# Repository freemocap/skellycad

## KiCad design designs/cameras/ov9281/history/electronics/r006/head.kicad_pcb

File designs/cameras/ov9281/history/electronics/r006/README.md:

# R06 power and ground routing

R06 adds saved copper to the R05 controller, sensor head and flex. It is a
checked routing draft, **not a fabrication release or a demonstrated camera**.
Open `controller.kicad_pcb` to inspect the power work, `head.kicad_pcb` for the
sensor, or `assembly-interconnect-study.kicad_pcb` for the flat assembly.
The combined assembly file is for inspection only; manufacture would use
three separate board definitions after the remaining engineering is complete.

## What changed

- Added 199 through vias and verified 219 component-pad-to-via paths.
- Added ground planes on the second copper layer of both rigid boards.
  All 75 controller ground pads join one electrical group. On the head,
  32 of 40 ground pads connect; eight sensor ground pads remain unconnected.
- Added 44 power branches: 37 on the third copper layer and seven on the back.
  Backside bridges join the controller's split 3.3 V fill. Of its 44 supply
  pads, 39 now connect together; five remain isolated.
- Added a continuous front-side ground plane and 18 vias to the flex.
  All 24 end-to-end conductors and all 18 ground contacts pass connectivity
  checks. Connector fingers remain exposed on the back.
- Defined provisional layer thicknesses in the native boards: 0.60 mm rigid
  and 0.10 mm flex for copper plus dielectric. These are design assumptions,
  not supplier-approved stackups. Mask, coverlay and adhesive remain additional.

The four-layer strategy follows Espressif's guidance: ground on layer 2 and
power on layer 3. The candidate inner core-supply and USB-input routes use
0.508 mm and 0.635 mm widths respectively. Other power routes use 0.254 mm.
The local surface escapes are still 0.15 mm; this does not establish compliance
with the recommended power widths, current capacity or decoupling-loop layout
[@esp32P4PcbLayout]. Circuit topology and supply sequencing still need review.

## Checks on the saved files

| KiCad unconnected items | R05 | R06 |
| --- | ---: | ---: |
| Controller | 195 | 54 |
| Sensor head | 93 | 47 |
| Flex | 8 | 0 |

These counts measure missing physical connections, not percentage completion.
There are no short-circuit or clearance violations under the inherited draft
rules. R06 still reports six open camera tracks and nine vias connected on only
one layer. These are unfinished routes, so this is **not a clean fabrication DRC**.
Schematic ERC reports zero violations under the inherited project settings;
ignored categories are visible in `checks/erc.rpt`.

`validation.json` records native-file hashes, 456 schematic-to-pad net checks,
24 assembled pin-alignment checks, retained R05 geometry and copper, and native
KiCad connectivity groups for every net. A one-pad net is trivially connected
on that board; it does not prove an external connection or a working function.
Filled region counts are geometry counts; physical copper connectivity is
checked separately, including the bridges between 3.3 V regions.

`power-routing.json` records each added escape and power route. It lists 33
pads without an escape and ten attempted power branches left unrouted. These
are diagnostic subsets of the DRC findings, not additional totals to add to
the table. Surface paths use straight or single-bend candidates; power paths
use collision-checked grid searches. Failure means the search did not find a
path, not that the circuit is impossible to route.

## What still separates this from a working camera

Complete the dense sensor/processor escapes, power circuits and camera/control
signal routes. Review placement and the fabrication process before changing
clearances or introducing finer vias. The 0.45 mm via lands and 0.20 mm drills
are provisional; this revision avoids via-in-pad. The small existing package
lands still require process review [@jlcThinPcbCapabilities].

The flex's solid plane changes its stiffness and transmission-line geometry.
No controlled impedance, supply-drop, thermal, flex-life or optical performance
is established. The wider R05 interface, 76 mm flat length, connector stiffener,
solder joint and strain relief also remain unfinished. Optics, IR illumination
and end-to-end capture firmware are separate unfinished parts of this camera.

Review scope, 2026-10-27: Espressif power and layer guidance, local native KiCad
DRC/ERC, filled-zone connectivity and retained R05 interface geometry. No
hardware, signal-integrity, optical or thermal measurements were performed.

## Reproduce and inspect

From the repository root, use KiCad 10's bundled Python to run
`designs/eye-camera-ov9281/build_r06.py --output generated/ov9281-r06-rebuild`.
Choose a new output directory; the builder refuses to replace one. Then run
`designs/eye-camera-ov9281/validate_r06.py --directory generated/ov9281-r06-rebuild`
with the same interpreter. The validator must finish successfully; inspect its
remaining unconnected items rather than treating success as release approval.

For a new FreeCAD review, run
`python designs/eye-camera-ov9281/export_r06_review.py --output generated/ov9281-r06-review-2`
from the repository root using ordinary Python. Choose another new output path
if that directory already exists. The script verifies the saved R06 hashes, exports
actual PCB solids and prepares `open-review.FCMacro`. Follow
`docs/development.md` to send that macro to the verified existing FreeCAD process.
It preserves open documents and saves a separate R06 FCStd. The review contains
substrates and copper, including internal layers; component bodies and optics
are absent. Its flex height is for viewing, not a validated mating height.

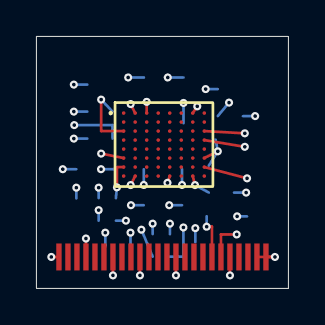
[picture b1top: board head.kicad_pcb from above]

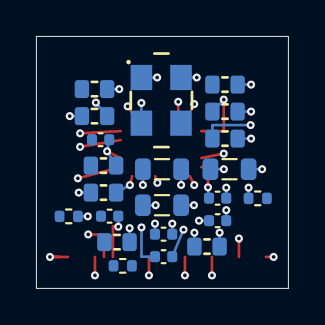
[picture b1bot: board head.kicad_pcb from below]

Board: 4 copper layers, 14.0 x 14.0 mm, 24 parts (22 on the bottom side), 24 nets.

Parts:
C7, C8, C10, C12, C13, C18, C19, C21, C33: C_1u_0603; C_0603_1608Metric
C9, C14, C15, C16, C17, C20: C_100n_6V3_0402; C_0402_1005Metric
J201: SOLDER FLEX / 24 contacts; Flex_Solder_24_P0.5_R05
L1, L2, L3: MLP2012S3R3MT; L_0805_2012Metric
R7, R8, R9: R_0R_0402; R_0402_1005Metric
U1: ImageSensor_OV9281; OV9281
Y1: 7C-24.000MBB-T; Oscillator_SMD_TXC_7C_5x3.2x1.2mm

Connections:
+1V2: J201.17, L1.1
+1V8: C33.1, J201.11, L2.1, Y1.1, Y1.4
+2V8: J201.19, L3.1
/CAM_L_CLK_N: J201.5, U1.H4
/CAM_L_CLK_P: J201.6, U1.G4
/CAM_L_D0_N: J201.2, U1.H3
/CAM_L_D0_P: J201.3, U1.G3
/CAM_L_D1_N: J201.8, U1.F5
/CAM_L_D1_P: J201.9, U1.G5
/CAM_NRST_1V8: J201.15, U1.A5
/M1_AVDD: C18.1, C19.1, C20.1, L3.2, R9.2, U1.B8, U1.C1, U1.G7, U1.G8
/M1_CAM_SCL_1V8: J201.12, U1.E4
/M1_CAM_SDA_1V8: J201.13, U1.A4
/M1_DOVDD: C13.1, C15.1, C16.1, L2.2, R7.1, U1.B7, U1.D3, U1.H2, U1.H6
/M1_DVDD: C9.1, C12.1, C14.1, L1.2, U1.A2, U1.B1, U1.B3, U1.C5, U1.D8, U1.F2, U1.F3, U1.G1, U1.G6, U1.H5
/M1_MCLK: U1.E2, Y1.3
/M1_PVDD: C17.1, R9.1, U1.D5
/M1_SID: R7.2, R8.1, U1.E1
/M1_VH: C21.1, U1.E8
/M1_VN1: C7.1, U1.D7
/M1_VN2: C8.1, U1.E7
/M1_VN3: C10.1, U1.F7
/M1_VSYNC_1V8_M: J201.16, U1.B5
GND: C7.2, C8.2, C9.2, C10.2, C12.2, C13.2, C14.2, C15.2, C16.2, C17.2, C18.2, C19.2, C20.2, C21.2, C33.2, J201.1, J201.4, J201.7, J201.10, J201.14, J201.18, J201.20, J201.23, J201.24, R8.2, U1.A3, U1.A7, U1.B2, U1.C8, U1.D2, U1.E3, U1.E5, U1.E6, U1.F1, U1.F4, U1.F6, U1.F8, U1.G2, U1.H7, Y1.2

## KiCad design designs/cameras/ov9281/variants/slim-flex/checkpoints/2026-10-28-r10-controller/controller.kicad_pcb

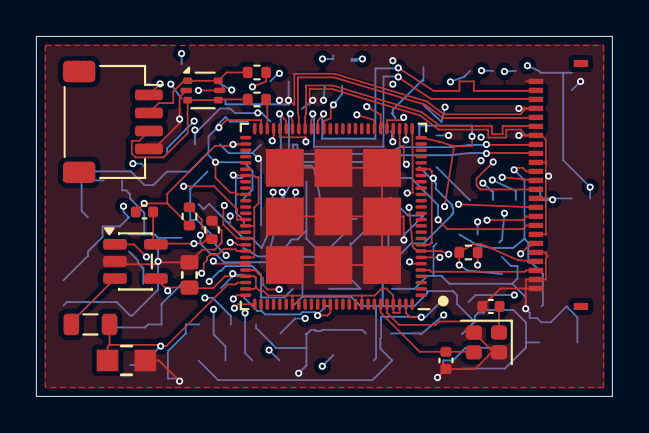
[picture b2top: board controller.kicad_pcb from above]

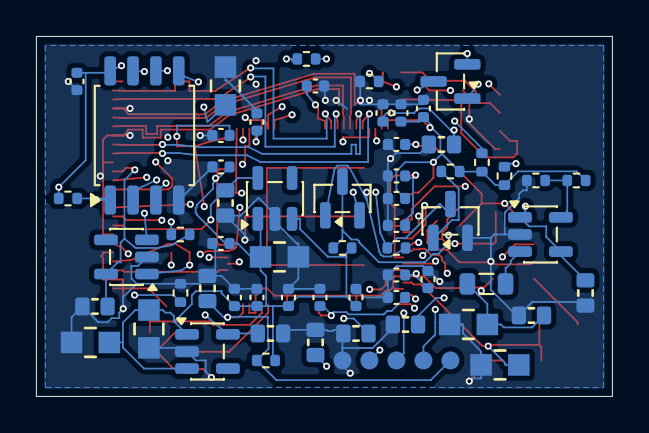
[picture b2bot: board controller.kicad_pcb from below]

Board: 6 copper layers, 32.0 x 20.0 mm, 77 parts (60 on the bottom side), 48 nets.

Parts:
C1, C2, C3: C_4u7_0805; C_0805_2012Metric
C4, C5, C6: C_1u_0603; C_0603_1608Metric
C101, C102: CL_TBD; C_0402_1005Metric
C103, C132, C135: 100n; C_0402_1005Metric
C104, C125, C126, C127, C133: 1u; C_0603_1608Metric
C105, C108, C136: 4.7u; C_0603_1608Metric
C106, C109: 22u; C_0805_2012Metric
C107: 22p; C_0402_1005Metric
C110: 100n / U101.9; C_0402_1005Metric
C111: 100n / U101.21; C_0402_1005Metric
C112: 100n / U101.26; C_0402_1005Metric
C113: 100n / U101.54; C_0402_1005Metric
C114: 100n / U101.62; C_0402_1005Metric
C115: 100n / U101.75; C_0402_1005Metric
C116: 100n / U101.76; C_0402_1005Metric
C117: 100n / U101.77; C_0402_1005Metric
C118: 100n / U101.85; C_0402_1005Metric
C119: 100n / U101.91; C_0402_1005Metric
C120: 100n / U101.96; C_0402_1005Metric
C121: 100n / U101.101; C_0402_1005Metric
C122: 100n / U101.102; C_0402_1005Metric
C123, C124: 10u; C_0805_2012Metric
C128: 100n / U101.30; C_0402_1005Metric
C129: 100n / U101.59; C_0402_1005Metric
C130: 100n / U101.67; C_0402_1005Metric
C131, C134: 10n; C_0402_1005Metric
J101: USB / JST 4-contact candidate; JST_SH_SM04B-SRSS-TB_1x04-1MP_P1.00mm_Horizontal
J102: FH34SRJ-24S-0.5SH(99); Hirose_FH34SRJ_24S_0.5SH_R05
J103: PROGRAM / RESET pads; ProgrammingPads_5x1mm_P1.5mm
L101, L102: 2.2u / Isat TBD; L_0805_2012Metric
Q101, Q102: BSS138; SOT-23
Q103: BSS138 / reset asserted HIGH; SOT-23
R101, R102, R103, R104, R117, R118: 10k; R_0402_1005Metric
R105, R106: 499k; R_0402_1005Metric
R107: 453k; R_0402_1005Metric
R108, R116: 100k; R_0402_1005Metric
R109, R110: 0; R_0402_1005Metric
R111: 4.02k 1%; R_0402_1005Metric
R112, R113, R114, R115: 4.7k; R_0402_1005Metric
U5: TLV73318PDBVT; SOT-23-5
U6: TLV73312PDBVT; SOT-23-5
U7: TLV73328PDBVT; SOT-23-5
U101: ESP32-P4NRW16X / v3.x; ESP32-P4
U102: W25Q32JVSS (4 MB candidate); SOIC-8_5.3x5.3mm_P1.27mm
U103: TLV62569DBV / core; SOT-23-5
U104: TLV62569DBV / system; SOT-23-5
U105: USBLC6-2P6; SOT-666
Y101: 40 MHz / CL TBD; Crystal_SMD_2016-4Pin_2.0x1.6mm

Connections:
+1V2: C6.1, J102.17, U6.5
+1V8: C5.1, J102.11, Q101.1, Q102.1, R112.1, R114.1, R117.1, U5.5
+2V8: C4.1, J102.19, U7.5
+3V3: C1.1, C2.1, C3.1, C105.1, C109.1, C110.1, C111.1, C114.1, C115.1, C117.1, C118.1, C120.1, C121.1, C122.1, C123.1, C134.1, C135.1, C136.1, J102.21, L102.2, R102.1, R103.1, R104.1, R107.1, R113.1, R115.1, R116.1, U5.1, U5.3, U6.1, U6.3, U7.1, U7.3, U101.9, U101.21, U101.51, U101.62, U101.75, U101.77, U101.85, U101.96, U101.101, U101.102, U103.4
/CAM_L_CLK_N: J102.5, U101.45
/CAM_L_CLK_P: J102.6, U101.44
/CAM_L_D0_N: J102.2, U101.42
/CAM_L_D0_P: J102.3, U101.43
/CAM_L_D1_N: J102.8, U101.46
/CAM_L_D1_P: J102.9, U101.47
/CAM_NRST_1V8: J102.15, Q103.3, R117.2
/CAM_RESET_ASSERT: Q103.1, R116.2, U101.6
/CAM_SCL_3V3: Q101.3, R113.2, U101.7
/CAM_SDA_3V3: Q102.3, R115.2, U101.8
/FLASH_CLK: U101.32, U102.6
/FLASH_CS: R101.2, U101.27, U102.1
/FLASH_D: U101.33, U102.5
/FLASH_HOLD: U101.31, U102.7
/FLASH_Q: U101.28, U102.2
/FLASH_WP: U101.29, U102.3
/LED_PWM: J102.22, U101.5
/M1_CAM_SCL_1V8: J102.12, Q101.2, R112.2
/M1_CAM_SDA_1V8: J102.13, Q102.2, R114.2
/M1_VSYNC_1V8_M: J102.16, R118.1
/P4_BOOT: J103.4, R103.2, U101.66
/P4_CSI_REXT: R111.1, U101.48
/P4_DOWNLOAD_ENABLE: R104.2, U101.68
/P4_EN: C104.1, J103.5, R102.2, U101.103
/P4_EN_DCDC: U101.79, U103.1
/P4_FB: C107.2, R105.2, R106.1, U101.78, U103.5
/P4_FLASH_VDD: C103.1, C125.1, C128.1, R101.1, U101.30, U101.71, U102.8
/P4_LDO4_UNUSED: C127.1, U101.74
/P4_MIPI_2V5: C131.1, C132.1, C133.1, U101.41, U101.73
/P4_PSRAM_VDD: C126.1, C129.1, C130.1, U101.59, U101.67, U101.72
/P4_SW: L101.1, U103.3
/P4_UART_RX: J103.3, U101.70
/P4_UART_TX: J103.2, U101.69
/P4_VDD_HP: C106.1, C107.1, C112.1, C113.1, C116.1, C119.1, C124.1, L101.2, R105.1, U101.26, U101.54, U101.76, U101.91
/P4_XTAL_N: C102.1, U101.99, Y101.3
/P4_XTAL_P: C101.1, U101.100, Y101.1
/SYS_FB: R107.2, R108.1, U104.5
/SYS_SW: L102.1, U104.3
/USB_DM: J101.2, R109.1, U105.1, U105.6
/USB_DM_CHIP: R109.2, U101.49
/USB_DP: J101.3, R110.1, U105.3, U105.4
/USB_DP_CHIP: R110.2, U101.50
/USB_VBUS: C108.1, J101.1, U104.1, U104.4, U105.5
GND: C1.2, C2.2, C3.2, C4.2, C5.2, C6.2, C101.2, C102.2, C103.2, C104.2, C105.2, C106.2, C108.2, C109.2, C110.2, C111.2, C112.2, C113.2, C114.2, C115.2, C116.2, C117.2, C118.2, C119.2, C120.2, C121.2, C122.2, C123.2, C124.2, C125.2, C126.2, C127.2, C128.2, C129.2, C130.2, C131.2, C132.2, C133.2, C134.2, C135.2, C136.2, J101.4, J102.1, J102.4, J102.7, J102.10, J102.14, J102.18, J102.20, J102.23, J102.24, J103.1, Q103.2, R106.2, R108.2, R111.2, R118.2, U5.2, U6.2, U7.2, U101.105, U102.4, U103.2, U104.2, U105.2, Y101.2, Y101.4

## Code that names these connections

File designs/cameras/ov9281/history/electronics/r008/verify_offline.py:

"""Recheck the selected artifact bundle; distinguish checks from release gates.

Does not alter native CAD files, flash devices, or report simulated pixels as
camera capture. Run after building both firmware variants with build.py.
"""
from pathlib import Path
import hashlib, json, re, subprocess, sys, xml.etree.ElementTree as ET
from system_analysis import analysis

HERE=Path(__file__).resolve().parent
ROOT=HERE.parents[1]
def sha(p):return hashlib.sha256(p.read_bytes()).hexdigest()

def verify():
    selection=json.loads((HERE/'controller-selection.json').read_text())
    board=HERE/Path(selection['validation']).parent
    validation=json.loads((board/'validation.json').read_text())
    for name,digest in validation['sha256'].items():assert sha(board/name)==digest,name
    parent=json.loads((board/'routing-r08.json').read_text())['parent_sha256']
    for name,digest in parent.items():assert sha(HERE/'electronics/r07'/name)==digest,name
    tree=ET.parse(board/'source-netlist.xml')
    nets={(q.get('ref'),q.get('pin')):n.get('name') for n in tree.findall('.//nets/net') for q in n}
    source=(HERE/'firmware/main/camera_main.c').read_text()
    bindings={'LED_GPIO':'/LED_PWM','RESET_ASSERT_GPIO':'/CAM_RESET_ASSERT',
              'SCL_GPIO':'/CAM_SCL_3V3','SDA_GPIO':'/CAM_SDA_3V3'}
    checked={}
    for constant,net in bindings.items():
        pin=re.search(r'\b'+constant+r'\s*=\s*(\d+)',source).group(1)
        assert nets[('U101',pin)]==net
        checked[constant]={'gpio':int(pin),'schematic_net':net}
    assert nets[('Q103','1')]==nets[('U101','6')]
    assert nets[('Q103','2')]=='GND'
    assert nets[('Q103','3')]==nets[('U1','A5')]
    assert nets[('R8','1')]==nets[('U1','E1')]
    assert nets[('R8','2')]=='GND'
    comps={x.get('ref'):x for x in tree.findall('.//components/comp')}
    assert comps['R7'].find("property[@name='dnp']") is not None
    assert comps['R8'].find("property[@name='dnp']") is None
    assert 'CONFIG_CAMERA_OV9281_SID_LOW=y' in (HERE/'firmware/sdkconfig.defaults').read_text()
    builds={}
    for mode in ['sensor','synthetic']:
        folder=ROOT/'generated'/('camera-firmware-'+mode)
        record=json.loads((folder/'build-report.json').read_text())
        assert record['compiled'] and not record['executed_on_hardware']
        for name,digest in record['source_sha256'].items():assert sha(HERE/'firmware'/name)==digest,name
        for name,digest in record['binary_sha256'].items():assert sha(folder/'build'/name)==digest,name
        config=(folder/'sdkconfig').read_text()
        assert 'CONFIG_ESP32P4_REV_MIN_FULL=300' in config
        assert 'CONFIG_TINYUSB_RHPORT_HS=y' in config
        assert ('CONFIG_SKELLY_SYNTHETIC=y' in config)==(mode=='synthetic')
        builds[mode]=record
    tests=subprocess.run([sys.executable,'-B','-m','unittest','discover','-s',str(HERE/'firmware/host'),'-p','test_*.py','-v'],capture_output=True,text=True)
    assert tests.returncode==0,tests.stdout+tests.stderr
    # The linked binary has no camera codec/IPA or radio blob library. This is
    # a narrow map check, not a legal audit of every toolchain runtime object.
    linkmap=(ROOT/'generated/camera-firmware-sensor/build/skelly_eye_camera.map').read_text()
    excluded=['libesp_ipa.a','libesp_h264.a','libnet80211.a','libpp.a','libcoexist.a','libesp_wifi.a']
    assert all(name not in linkmap for name in excluded)
    inventory=json.loads((board/'inventory.json').read_text())
    assert len(inventory['items'])==sum(x['footprints'] for x in validation['boards'].values())
    mechanical_folder=ROOT/'generated/ov9281-r08-desktop'
    mechanical=json.loads((mechanical_folder/'review-status.json').read_text())
    export_sources=json.loads((mechanical_folder/'source-record.json').read_text())
    assert export_sources['native_sha256']==validation['sha256']
    assert mechanical['pin_xy_alignment_checks']==24
    for name,entry in mechanical['boards'].items():
        assert entry['valid'] and entry['solids']>0
        assert sha(mechanical_folder/(name+'.step'))==entry['source_sha256']
    mechanical['saved_document_sha256']=sha(mechanical_folder/'OV9281-R08-PCB-REVIEW.FCStd')
    oscillator={'reference':'Y1','value':comps['Y1'].findtext('value'),
        'supply_net':nets[('Y1','4')],'description':comps['Y1'].findtext('description'),
        'status':'Unresolved 3.3 V part metadata versus 1.8 V supply; verify exact part and land pattern before assembly'}
    result={'revision':selection['revision'],'offline_checks_passed':True,
        'fabrication_ready':False,'physical_camera_demonstrated':False,
        'native_file_hashes':validation['sha256'],'firmware_gpio_bindings':checked,
        'reset_inversion_and_sid_low_netlist_checks':True,'builds':builds,
        'host_test_output':tests.stderr,'excluded_link_libraries_checked':excluded,
        'unconnected_items':{n:d['unconnected_items'] for n,d in validation['boards'].items()},
        'oscillator_selection_conflict':oscillator,'analysis':analysis(),'mechanical_review':mechanical,
        'remaining_computer_work':['Finish PCB routing including MIPI/USB constraints and flash.',
            'Resolve Y1 voltage/land-pattern conflict; complete component and power-sequencing audit.',
            'Complete illumination circuit and select lens, filter and mechanical interfaces.',
            'Define manufacturer stackup, impedance and assembly constraints.',
            'Resolve 400/800 Mbps receiver timing discrepancy; add exposure/gain controls and continuous transport.'],
        'hardware_required':['Power sequencing/current/thermal measurements.',
            'Actual RAW8 frames, CSI timing, USB enumeration and throughput.',
            '940 nm focus/field-of-view and LED optical exposure measurements.',
            'Assembly fit, bending, mass and durability.']}
    dest=HERE/'verification';dest.mkdir(exist_ok=True)
    (dest/'offline-report.json').write_text(json.dumps(result,indent=2)+'\n')
    print(json.dumps({k:result[k] for k in ['revision','offline_checks_passed','fabrication_ready','physical_camera_demonstrated','unconnected_items']},indent=2))

if __name__=='__main__':verify()

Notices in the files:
parts and their libraries:
License: Apache-2.0
